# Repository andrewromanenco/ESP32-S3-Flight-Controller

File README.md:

# ESP32-S3 Flight Controller

A flight-controller board built around the
ESP32-S3-WROOM-1-N16R8 module and an ICM-42686-P six-axis IMU. The repository
contains the complete KiCad design files and manufacturing outputs needed to
inspect, modify, or assemble the board.

## Hardware overview

- ESP32-S3-WROOM-1-N16R8 module with 16 MB flash and 8 MB PSRAM
- ICM-42686-P three-axis gyroscope and three-axis accelerometer
- USB-C connection for power and native USB programming
- 5 V input with onboard 3.3 V regulation
- JST-GH connections for SPI, I2C, UART, power, and GPIO
- BOOT and RESET controls
- Four-layer PCB design

## Repository contents

- `ESP32-IMU.kicad_pro` - KiCad project
- `ESP32-IMU.kicad_sch` - schematic
- `ESP32-IMU.kicad_pcb` - PCB layout
- `ESP32-IMU.csv` - exported bill of materials
- `gerbers-and-bom/Gerbers.zip` - packaged manufacturing files
- `gerbers-and-bom/Gerbers/` - Gerbers, drill files, placement data, and
  PCBWay-formatted BOM

The design was created with KiCad 10.

## Programming

The ESP32-S3 can be programmed directly through the board's USB-C connector.

Alternatively, an external CP2102 USB-to-UART adapter can be connected to the
UART0 header. When using UART0 exclusively for programming, the USB connector
and its associated USB protection components do not need to be populated. Make
sure the adapter uses 3.3 V logic levels and connect TX to RX, RX to TX, and GND
to GND.

## Manufacturing

Gerbers, drill files, component placement data, and the BOM
are available in [`gerbers-and-bom/Gerbers/`](gerbers-and-bom/Gerbers/). A
ready-to-order copy of the project is also available on
[PCBWay](https://www.pcbway.com/project/shareproject/ESP32_IMU_kicad_pcb_3eb42851.html).

Review the fabrication outputs and assembly options before ordering, especially
if components are intentionally left unpopulated.

## Disclaimer

This is an experimental hardware design. Review the schematic, PCB layout,
component ratings, and power connections before assembly. Test the completed
board safely on the bench before using it.

## License

This hardware design and its associated design files are licensed under the
[CERN Open Hardware Licence Version 2 - Permissive
(CERN-OHL-P-2.0)](LICENSE).

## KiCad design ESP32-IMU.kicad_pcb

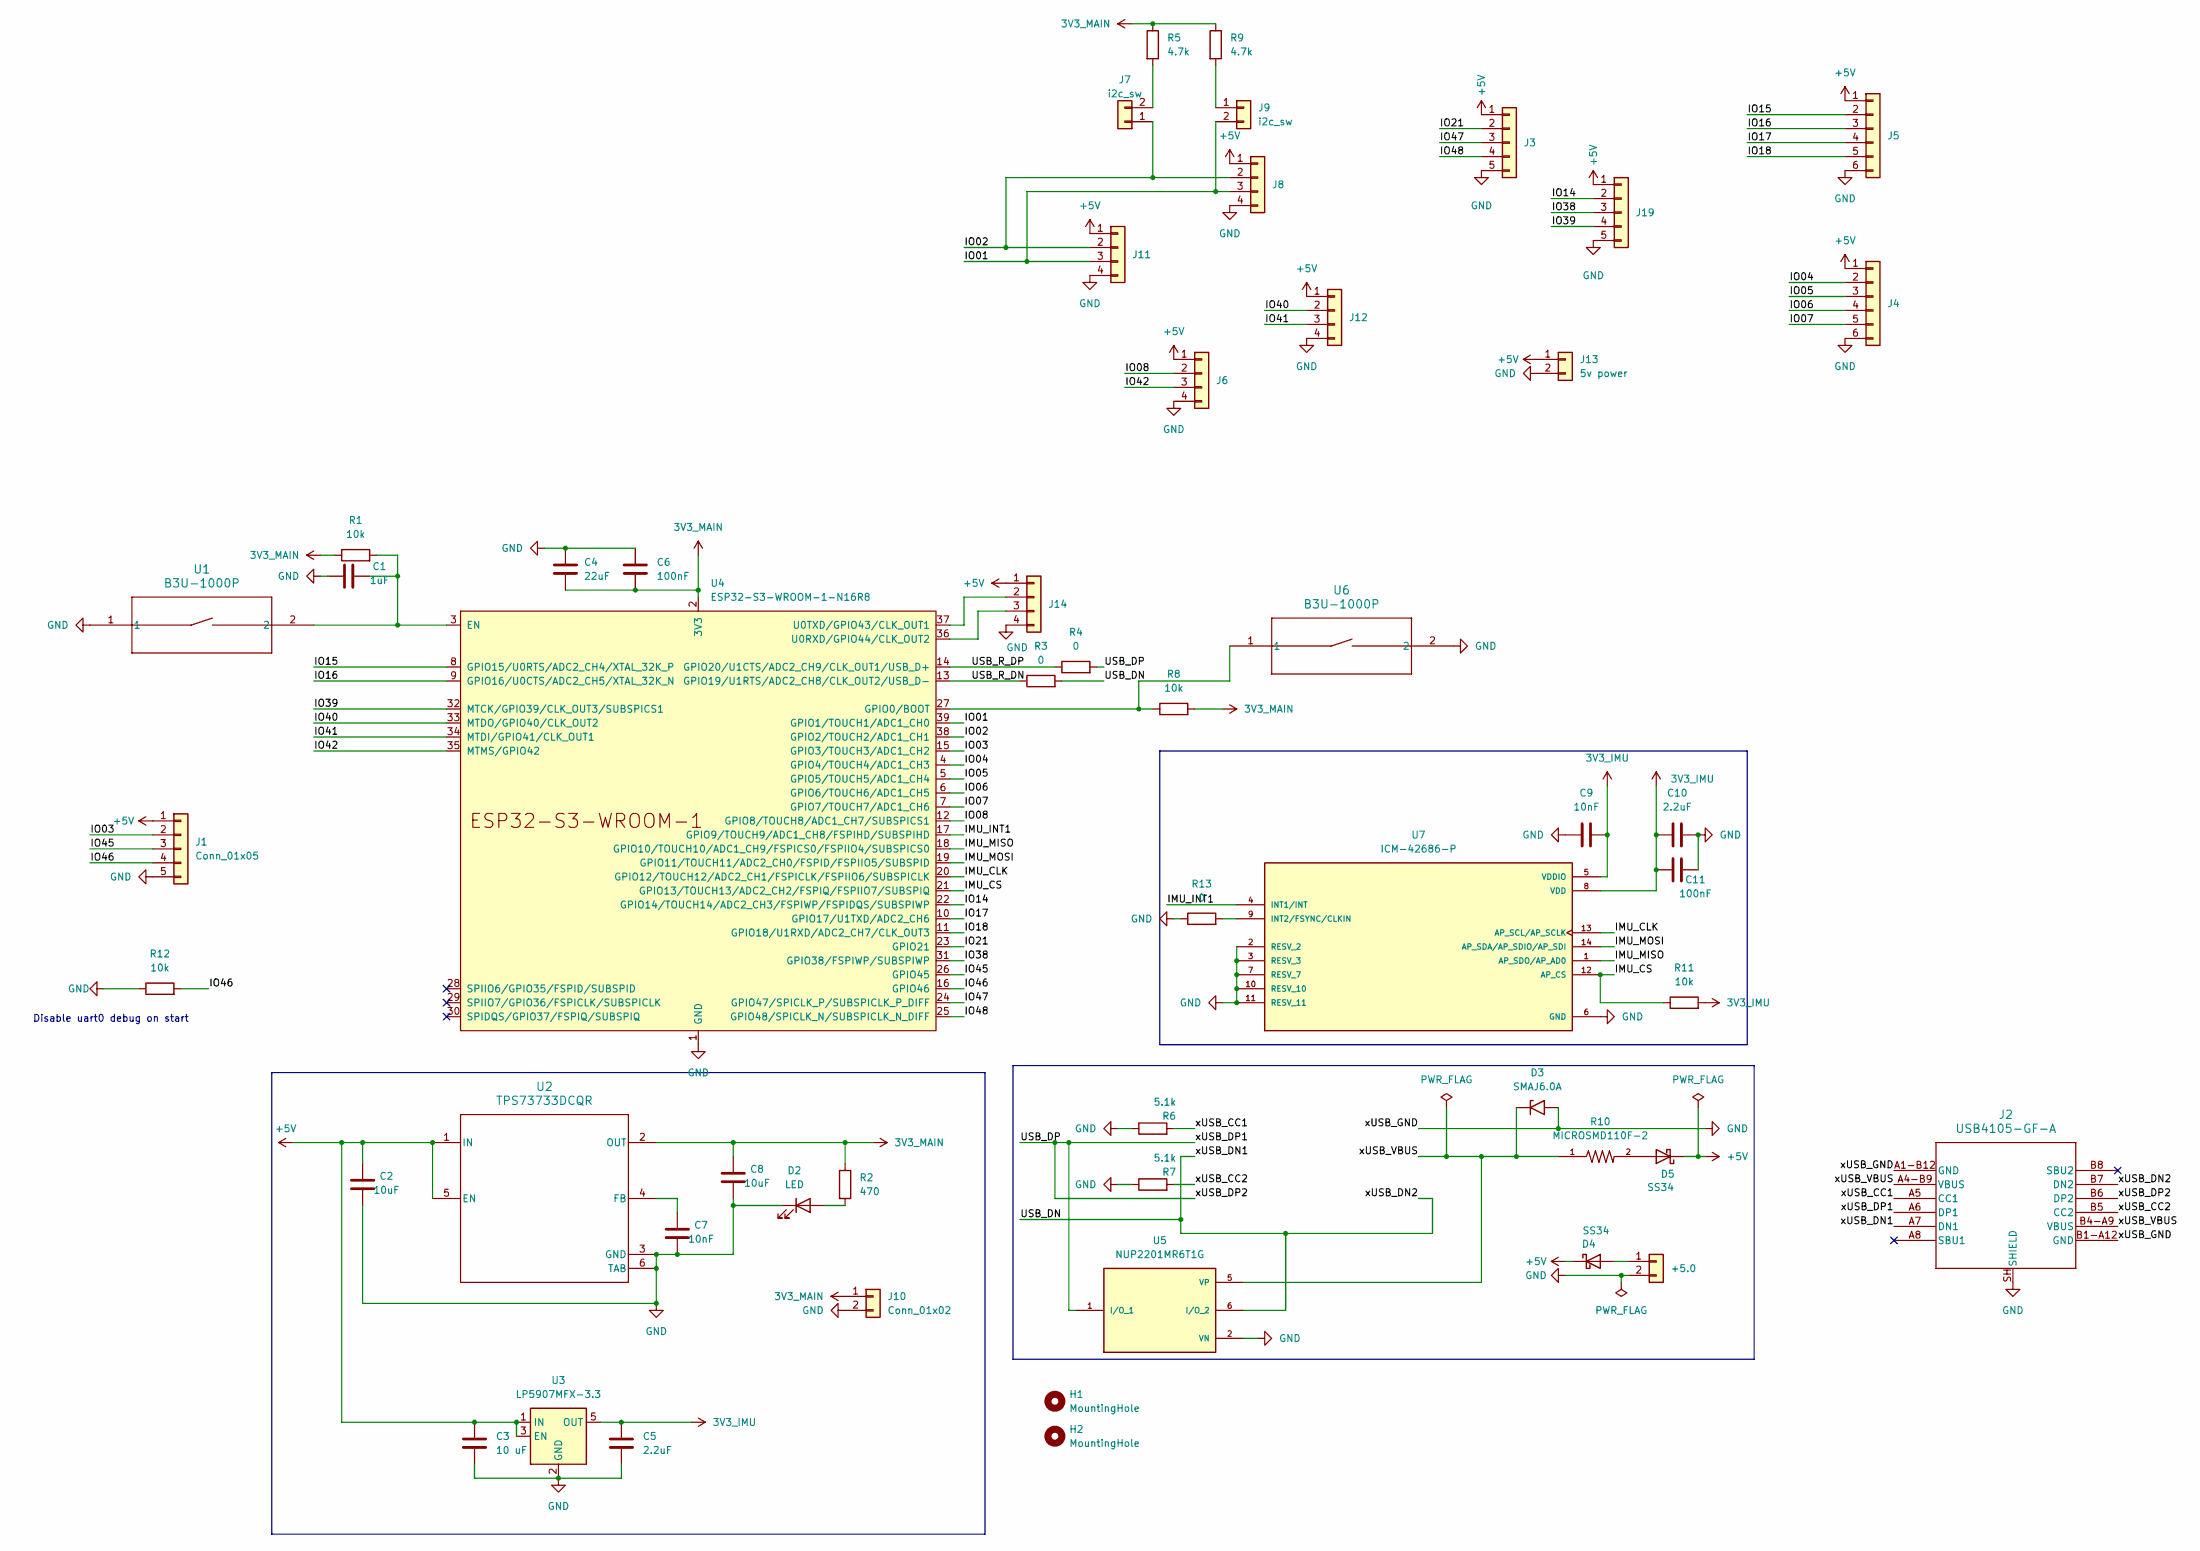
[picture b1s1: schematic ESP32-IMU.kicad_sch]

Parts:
+5.0: 5-in; CONN_OSTVN02A150_OST
C1: 1uF; C_0603_1608Metric; MPN CC0603KRX7R7BB105
C2, C8: 10uF; C_0805_2012Metric; MPN CL21A106KPFNNNE
C3: 10 uF; C_0805_2012Metric; MPN CL21B106KOQNNNE
C4: 22uF; C_1206_3216Metric; MPN CL31B226KQHNNNE
C5, C10: 2.2uF; C_0603_1608Metric; MPN CL10B225KP8NFNC
C6, C11: 100nF; C_0603_1608Metric; MPN CL10B104KO8NNNC
C7: 10nF; C_0603_1608Metric; MPN CL10B103KO8WPNC
C9: 10nF; C_0603_1608Metric; MPN C0603C103K5RACTU
D2: LED; LED_0603_1608Metric; MPN SML-D12U1WT86
D3: SMAJ6.0A; D_SMA; MPN SMAJ6.0A
D4, D5: SS34; D_SMA; MPN SS34LW
H1, H2: MountingHole; MountingHole_2.2mm_M2
J1: Conn_01x05; JST_GH_BM05B-GHS-TBT_1x05-1MP_P1.25mm_Vertical
J2: USB4105-GF-A; USB4105_GCT; MPN USB4105-GF-A-120
J3, J19: Conn_01x05; JST_GH_SM05B-GHS-TB_1x05-1MP_P1.25mm_Horizontal
J4, J5: spi; JST_GH_SM06B-GHS-TB_1x06-1MP_P1.25mm_Horizontal
J6: uart1; JST_GH_SM04B-GHS-TB_1x04-1MP_P1.25mm_Horizontal
J7, J9: i2c_sw; SolderJumper-2_P1.3mm_Bridged_RoundedPad1.0x1.5mm
J8, J11: i2c; JST_GH_SM04B-GHS-TB_1x04-1MP_P1.25mm_Horizontal
J10: Conn_01x02; JST_GH_BM02B-GHS-TBT_1x02-1MP_P1.25mm_Vertical
J12: uart2; JST_GH_SM04B-GHS-TB_1x04-1MP_P1.25mm_Horizontal
J13: 5v power; JST_GH_SM02B-GHS-TB_1x02-1MP_P1.25mm_Horizontal
J14: uart0; JST_GH_SM04B-GHS-TB_1x04-1MP_P1.25mm_Horizontal
R1, R8, R11, R12: 10k; R_0603_1608Metric; MPN RM06F1002CT
R2: 470; R_0603_1608Metric; MPN CRGCQ0603F470R
R3, R4, R13: 0; R_0603_1608Metric; MPN RC0603JR-070RL
R5, R9: 4.7k; R_0603_1608Metric; MPN RMCF0603FT4K70
R6, R7: 5.1k; R_0603_1608Metric; MPN RC0603FR-075K1L
R10: MICROSMD110F-2; RESC3125X65N; MPN MICROSMD110F-2
U1, U6: B3U-1000P
U2: TPS73733DCQR; DCQ0006A; MPN TPS73733DCQR
U3: LP5907MFX-3.3; SOT-23-5; MPN LP5907MFX-3.3/NOPB
U4: ESP32-S3-WROOM-1-N16R8; ESP32-S3-WROOM-1; MPN ESP32-S3-WROOM-1-N16R8
U5: NUP2201MR6T1G; SOT95P275X110-6N; PARTREV 5; DigiKey_Part_Number NUP2201MR6T1GOSCT-ND
U7: ICM-42686-P; XDCR_ICM-42686-P; PARTREV 1.4; DigiKey_Part_Number 1428-ICM-42686-PCT-ND

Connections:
3V3_IMU: C5.1, C9.2, C10.1, C11.2, R11.2, U3.5 (OUT), U7.5 (VDDIO), U7.8 (VDD)
3V3_MAIN: C4.2, C6.1, C8.2, J10.1, R1.1, R2.1, R5.1, R8.2, R9.1, U2.2 (OUT), U4.2 (3V3)
+5V: C2.2, C3.1, D4.1 (K), D5.1 (K), J1.1, J3.1, J4.1, J5.1, J6.1, J8.1, J11.1, J12.1, J13.1, J14.1, J19.1, U2.1 (IN), U2.5 (EN), U3.1 (IN), U3.3 (EN)
/IMU_CLK: U4.20 (GPIO12/TOUCH12/ADC2_CH1/FSPICLK/FSPIIO6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), U7.13 (AP_SCL/AP_SCLK)
/IMU_CS: R11.1, U4.21 (GPIO13/TOUCH13/ADC2_CH2/FSPIQ/FSPIIO7/S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), U7.12 (AP_CS)
/IMU_INT1: U4.17 (GPIO9/TOUCH9/ADC1_CH8/FSPIHD/SUBSPIHD), U7.4 (INT1/INT)
/IMU_MISO: U4.18 (GPIO10/TOUCH10/ADC1_CH9/FSPICS0/FSPIIO4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), U7.1 (AP_SDO/AP_AD0)
/IMU_MOSI: U4.19 (GPIO11/TOUCH11/ADC2_CH0/FSPID/FSPIIO5/S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), U7.14 (AP_SDA/AP_SDIO/AP_SDI)
/IO01: J8.3, J9.2, J11.3, U4.39 (GPIO1/TOUCH1/ADC1_CH0)
/IO02: J7.1, J8.2, J11.2, U4.38 (GPIO2/TOUCH2/ADC1_CH1)
/IO03: J1.2, U4.15 (GPIO3/TOUCH3/ADC1_CH2)
/IO04: J4.2, U4.4 (GPIO4/TOUCH4/ADC1_CH3)
/IO05: J4.3, U4.5 (GPIO5/TOUCH5/ADC1_CH4)
/IO06: J4.4, U4.6 (GPIO6/TOUCH6/ADC1_CH5)
/IO07: J4.5, U4.7 (GPIO7/TOUCH7/ADC1_CH6)
/IO08: J6.2, U4.12 (GPIO8/TOUCH8/ADC1_CH7/SUBSPICS1)
/IO14: J19.2, U4.22 (GPIO14/TOUCH14/ADC2_CH3/FSPIWP/FSPIDQS/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)
/IO15: J5.2, U4.8 (GPIO15/U0RTS/ADC2_CH4/XTAL_32K_P)
/IO16: J5.3, U4.9 (GPIO16/U0CTS/ADC2_CH5/XTAL_32K_N)
/IO17: J5.4, U4.10 (GPIO17/U1TXD/ADC2_CH6)
/IO18: J5.5, U4.11 (GPIO18/U1RXD/ADC2_CH7/CLK_OUT3)
/IO21: J3.2, U4.23 (GPIO21)
/IO38: J19.3, U4.31 (GPIO38/FSPIWP/SUBSPIWP)
/IO39: J19.4, U4.32 (MTCK/GPIO39/CLK_OUT3/SUBSPICS1)
/IO40: J12.2, U4.33 (MTDO/GPIO40/CLK_OUT2)
/IO41: J12.3, U4.34 (MTDI/GPIO41/CLK_OUT1)
/IO42: J6.3, U4.35 (MTMS/GPIO42)
/IO45: J1.3, U4.26 (GPIO45)
/IO46: J1.4, R12.2, U4.16 (GPIO46)
/IO47: J3.3, U4.24 (GPIO47/SPICLK_P/SUBSPICLK_P_DIFF)
/IO48: J3.4, U4.25 (GPIO48/SPICLK_N/SUBSPICLK_N_DIFF)
/USB_DN: J2.A7 (DN1), J2.B7 (DN2), R3.2, U5.6 (I/O_2)
/USB_DP: J2.A6 (DP1), J2.B6 (DP2), R4.2, U5.1 (I/O_1)
/USB_R_DN: R3.1, U4.13 (GPIO19/U1RTS/ADC2_CH8/CLK_OUT2/USB_D-)
/USB_R_DP: R4.1, U4.14 (GPIO20/U1CTS/ADC2_CH9/CLK_OUT1/USB_D+)
/xUSB_CC1: J2.A5 (CC1), R6.2
/xUSB_CC2: J2.B5 (CC2), R7.2
/xUSB_VBUS: D3.1 (A1), J2.A4-B9 (VBUS), J2.B4-A9 (VBUS), R10.1, U5.5 (VP)
GND: +5.0.2, C1.1, C2.1, C3.2, C4.1, C5.2, C6.2, C7.1, C8.1, C9.1, C10.2, C11.1, D2.1 (K), D3.2 (A2), J1.5, J2.A1-B12 (GND), J2.B1-A12 (GND), J2.SH (SHIELD), J3.5, J4.6, J5.6, J6.4, J8.4, J10.2, J11.4, J12.4, J13.2, J14.4, J19.5, R6.1, R7.1, R12.1, R13.1, U1.1, U2.3 (GND), U2.6 (TAB), U3.2 (GND), U4.1 (GND), U4.40 (GND), U4.41 (GND), U5.2 (VN), U6.2, U7.2 (RESV_2), U7.3 (RESV_3), U7.6 (GND), U7.7 (RESV_7), U7.10 (RESV_10), U7.11 (RESV_11)
unnamed: +5.0.1, D4.2 (A)
unnamed: D2.2 (A), R2.2
unnamed: D5.2 (A), R10.2
unnamed: J7.2, R5.2
unnamed: J9.1, R9.2
unnamed: J14.2, U4.37 (U0TXD/GPIO43/CLK_OUT1)
unnamed: J14.3, U4.36 (U0RXD/GPIO44/CLK_OUT2)
unnamed: C7.2, U2.4 (FB)
unnamed: C1.2, R1.2, U1.2, U4.3 (EN)
unnamed: R8.1, U4.27 (GPIO0/BOOT), U6.1
unnamed: R13.2, U7.9 (INT2/FSYNC/CLKIN)

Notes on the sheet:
Disable uart0 debug on start

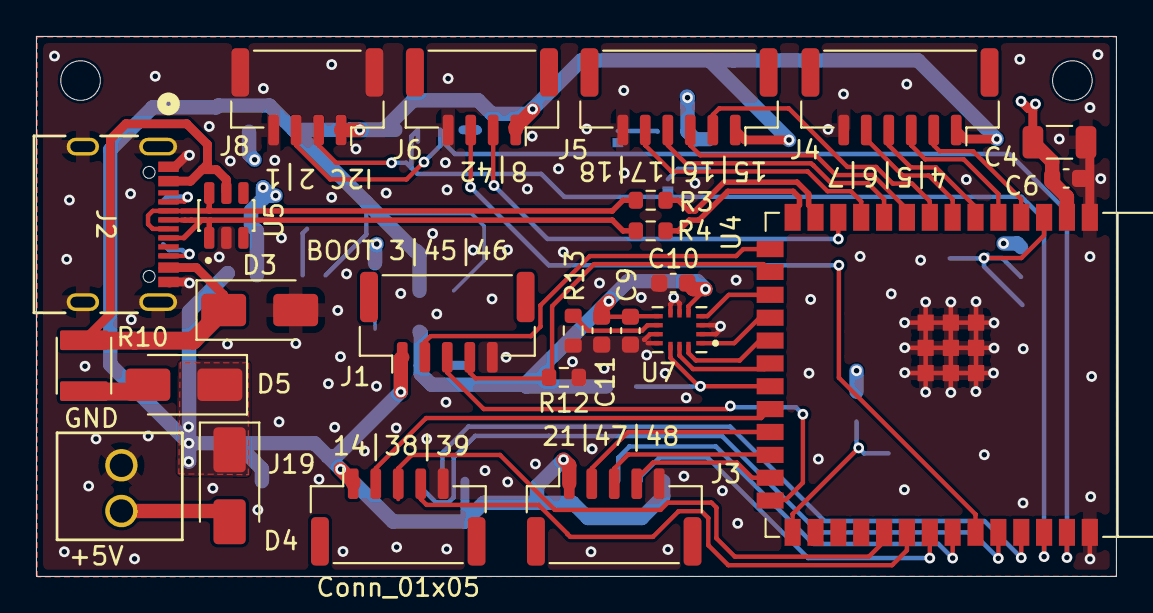
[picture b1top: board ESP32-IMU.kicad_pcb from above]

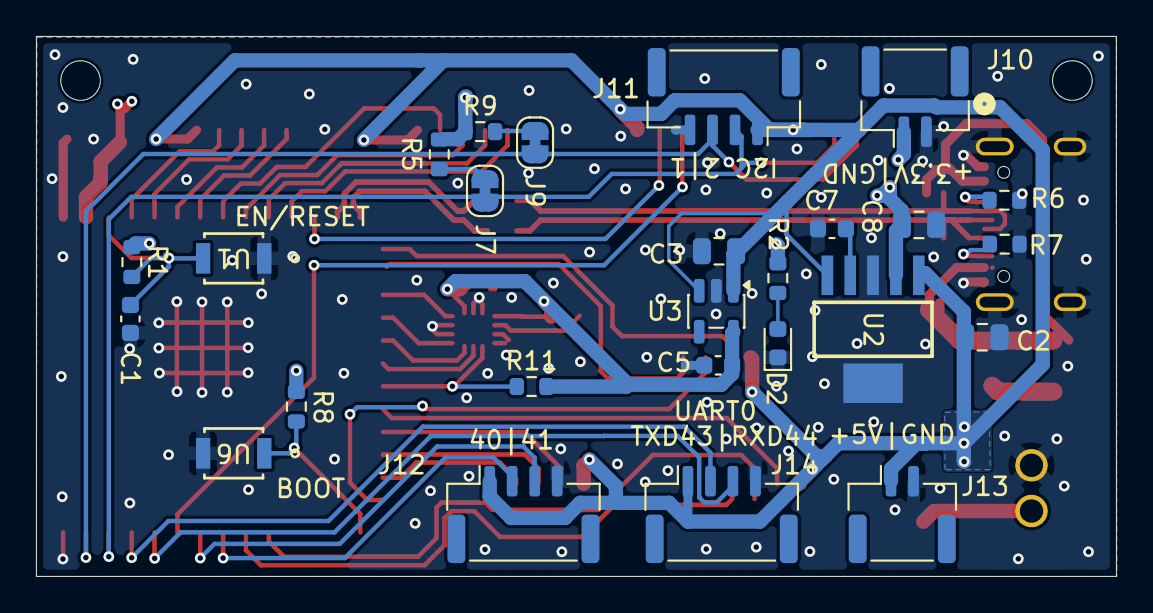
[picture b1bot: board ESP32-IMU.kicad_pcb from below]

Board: 4 copper layers, 60.0 x 30.0 mm, 53 parts (26 on the bottom side), 50 nets.

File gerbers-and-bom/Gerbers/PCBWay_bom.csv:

Designator,Quantity,Value,Footprint,Package,MPN,DNP,Mount_Type,Description,KiLib_Generator,Sim.Pins,DigiKey_Part_Number,SnapEDA_Link,Check_prices,STANDARD,PARTREV,MF,MP,MANUFACTURER,MAXIMUM_PACKAGE_HEIGHT,CREATOR,UNIT
+5.0,1,5-in,CONN_OSTVN02A150_OST,,,,tht,"Generic connector, single row, 01x02, script generated (kicad-library-utils/schlib/autogen/connector/)",,,,,,,,,,,,,
C1,1,1uF,C_0603_1608Metric,,CC0603KRX7R7BB105,,smt,CAP CER 1UF 16V X7R 0603,SMD_2terminal_chip_molded,,,,,,,,,,,,
"C10, C5",2,2.2uF,C_0603_1608Metric,,CL10B225KP8NFNC,,smt,Unpola2.2 µF ±10% 10V Ceramic Capacitor X7R 0603 (1608 Metric)rized capacitor,SMD_2terminal_chip_molded,,,,,,,,,,,,
"C11, C6",2,100nF,C_0603_1608Metric,,CL10B104KO8NNNC,,smt,100nF 16V X7R 0603,SMD_2terminal_chip_molded,,,,,,,,,,,,
"C2, C8",2,10uF,C_0805_2012Metric,,CL21A106KPFNNNE,,smt,CAP CER 10UF 10V X5R 0805,SMD_2terminal_chip_molded,,,,,,,,,,,,
C3,1,10 uF,C_0805_2012Metric,,CL21B106KOQNNNE,,smt,CAP CER 10UF 16V X7R 0805,SMD_2terminal_chip_molded,,,,,,,,,,,,
C4,1,22uF,C_1206_3216Metric,,CL31B226KQHNNNE,,smt,22 µF ±10% 6.3V Ceramic Capacitor X7R 1206 (3216 Metric),SMD_2terminal_chip_molded,,,,,,,,,,,,
C7,1,10nF,C_0603_1608Metric,,CL10B103KO8WPNC,,smt,CAP CER 10NF 16V X7R 0603,SMD_2terminal_chip_molded,,,,,,,,,,,,
C9,1,10nF,C_0603_1608Metric,,C0603C103K5RACTU,,smt,CAP CER 10000PF 50V X7R 0603,SMD_2terminal_chip_molded,,,,,,,,,,,,
D2,1,LED,LED_0603_1608Metric,,SML-D12U1WT86,,smt,"Light emitting diode, RED",SMD_2terminal_chip_molded,1=K 2=A,,,,,,,,,,,
D3,1,SMAJ6.0A,D_SMA,,SMAJ6.0A,,smt,"400W unidirectional Transient Voltage Suppressor, 6.0Vr, SMA(DO-214AC)",,,,,,,,,,,,,
"D4, D5",2,SS34,D_SMA,,SS34LW,,smt,"40V 3A Schottky Diode, SMA",,,,,,,,,,,,,
J1,1,Conn_01x05,JST_GH_BM05B-GHS-TBT_1x05-1MP_P1.25mm_Vertical,,,,smt,"Generic connector, single row, 01x05, script generated (kicad-library-utils/schlib/autogen/connector/)",connector/SMD_single_row_plus_mounting_pad,,,,,,,,,,,,
J10,1,Conn_01x02,JST_GH_BM02B-GHS-TBT_1x02-1MP_P1.25mm_Vertical,,,,smt,"Generic connector, single row, 01x02, script generated (kicad-library-utils/schlib/autogen/connector/)",connector/SMD_single_row_plus_mounting_pad,,,,,,,,,,,,
"J11, J8",2,i2c,JST_GH_SM04B-GHS-TB_1x04-1MP_P1.25mm_Horizontal,,,,smt,"Generic connector, single row, 01x04, script generated (kicad-library-utils/schlib/autogen/connector/)",connector/SMD_single_row_plus_mounting_pad,,,,,,,,,,,,
J12,1,uart2,JST_GH_SM04B-GHS-TB_1x04-1MP_P1.25mm_Horizontal,,,,smt,"Generic connector, single row, 01x04, script generated (kicad-library-utils/schlib/autogen/connector/)",connector/SMD_single_row_plus_mounting_pad,,,,,,,,,,,,
J13,1,5v power,JST_GH_SM02B-GHS-TB_1x02-1MP_P1.25mm_Horizontal,,,,smt,"Generic connector, single row, 01x02, script generated (kicad-library-utils/schlib/autogen/connector/)",connector/SMD_single_row_plus_mounting_pad,,,,,,,,,,,,
J14,1,uart0,JST_GH_SM04B-GHS-TB_1x04-1MP_P1.25mm_Horizontal,,,,smt,"Generic connector, single row, 01x04, script generated (kicad-library-utils/schlib/autogen/connector/)",connector/SMD_single_row_plus_mounting_pad,,,,,,,,,,,,
"J19, J3",2,Conn_01x05,JST_GH_SM05B-GHS-TB_1x05-1MP_P1.25mm_Horizontal,,,,smt,"Generic connector, single row, 01x05, script generated (kicad-library-utils/schlib/autogen/connector/)",connector/SMD_single_row_plus_mounting_pad,,,,,,,,,,,,
J2,1,USB4105-GF-A,USB4105_GCT,,USB4105-GF-A-120,,smt,,,,,,,,,,,,,,
"J4, J5",2,spi,JST_GH_SM06B-GHS-TB_1x06-1MP_P1.25mm_Horizontal,,,,smt,"Generic connector, single row, 01x06, script generated (kicad-library-utils/schlib/autogen/connector/)",connector/SMD_single_row_plus_mounting_pad,,,,,,,,,,,,
J6,1,uart1,JST_GH_SM04B-GHS-TB_1x04-1MP_P1.25mm_Horizontal,,,,smt,"Generic connector, single row, 01x04, script generated (kicad-library-utils/schlib/autogen/connector/)",connector/SMD_single_row_plus_mounting_pad,,,,,,,,,,,,
"J7, J9",2,i2c_sw,SolderJumper-2_P1.3mm_Bridged_RoundedPad1.0x1.5mm,,,,tht,"Generic connector, single row, 01x02, script generated (kicad-library-utils/schlib/autogen/connector/)",,,,,,,,,,,,,
"R1, R11, R12, R8",4,10k,R_0603_1608Metric,,RM06F1002CT,,smt,RES 10K OHM 1% 1/10W 0603,SMD_2terminal_chip_molded,,,,,,,,,,,,
R10,1,MICROSMD110F-2,RESC3125X65N,,MICROSMD110F-2,,smt,,,,,,,,,,,,,,
"R13, R3, R4",3,0,R_0603_1608Metric,,RC0603JR-070RL,,smt,"0 Ohms Jumper 0.1W, 1/10W Chip Resistor 0603 (1608 Metric) Moisture Resistant Thick Film",SMD_2terminal_chip_molded,,,,,,,,,,,,
R2,1,470,R_0603_1608Metric,,CRGCQ0603F470R,,smt,Resistor,SMD_2terminal_chip_molded,,,,,,,,,,,,
"R5, R9",2,4.7k,R_0603_1608Metric,,RMCF0603FT4K70,,smt,"Resistor, 4.7k",SMD_2terminal_chip_molded,,,,,,,,,,,,
"R6, R7",2,5.1k,R_0603_1608Metric,,RC0603FR-075K1L,,smt,"Resistor, 5.1k",SMD_2terminal_chip_molded,,,,,,,,,,,,
"U1, U6",2,B3U-1000P,B3U-1000P,,,,smt,,,,,,,,,,,,,,
U2,1,TPS73733DCQR,DCQ0006A,,TPS73733DCQR,,smt,,,,,,,,,,,,,,
U3,1,LP5907MFX-3.3,SOT-23-5,,LP5907MFX-3.3/NOPB,,smt,"250-mA Ultra-Low-Noise Low-IQ LDO, 3.3V, SOT-23",package/gullwing,,,,,,,,,,,,
U4,1,ESP32-S3-WROOM-1-N16R8,ESP32-S3-WROOM-1,,ESP32-S3-WROOM-1-N16R8,,smt,"2.4 GHz WiFi (802.11 b/g/n) and Bluetooth ® 5 (LE) module Built around ESP32S3 series of SoCs, Xtensa ® dualcore 32bit LX7 microprocessor Flash up to 16 MB, PSRAM up to 8 MB 36 GPIOs, rich set of peripherals Onboard PCB antenna",,,,,,,,,,,,,
U5,1,NUP2201MR6T1G,SOT95P275X110-6N,TSOP-6 ON Semiconductor,NUP2201MR6T1G,,smt,"NUP2201MR6T1G, Dual Uni-Directional TVS Diode Array, 500W, 6-Pin TSOP | ON Semiconductor NUP2201MR6T1G",,,NUP2201MR6T1GOSCT-ND,https://www.snapeda.com/parts/NUP2201MR6T1G/Onsemi/view-part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,https://www.snapeda.com/parts/NUP2201MR6T1G/Onsemi/view-part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,IPC 7351B,5,ON Semiconductor,NUP2201MR6T1G,ON SEMICONDUCTOR,,,
U7,1,ICM-42686-P,XDCR_ICM-42686-P,Package,ICM-42686-P,,smt,"Accelerometer, Gyroscope, 3 Axis Sensor I²C, I3C℠, SPI Output",,,1428-ICM-42686-PCT-ND,https://www.snapeda.com/parts/ICM-42686-P/TDK/view-part/?ref=snap,https://www.snapeda.com/parts/ICM-42686-P/TDK/view-part/?ref=eda,Manufacturer Recommendations,1.4,TDK InvenSense,ICM-42686-P,TDK InvenSense,0.97mm,ASHISH,mm
